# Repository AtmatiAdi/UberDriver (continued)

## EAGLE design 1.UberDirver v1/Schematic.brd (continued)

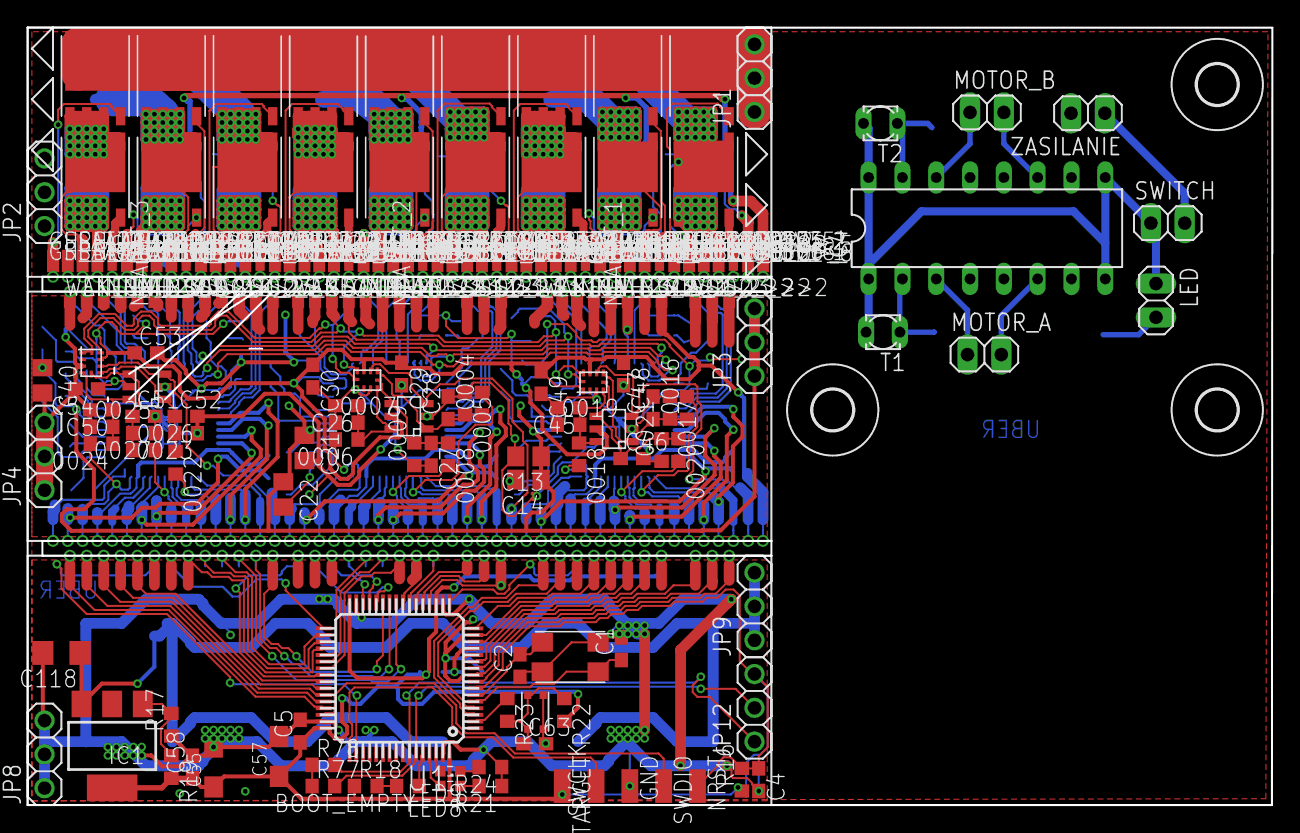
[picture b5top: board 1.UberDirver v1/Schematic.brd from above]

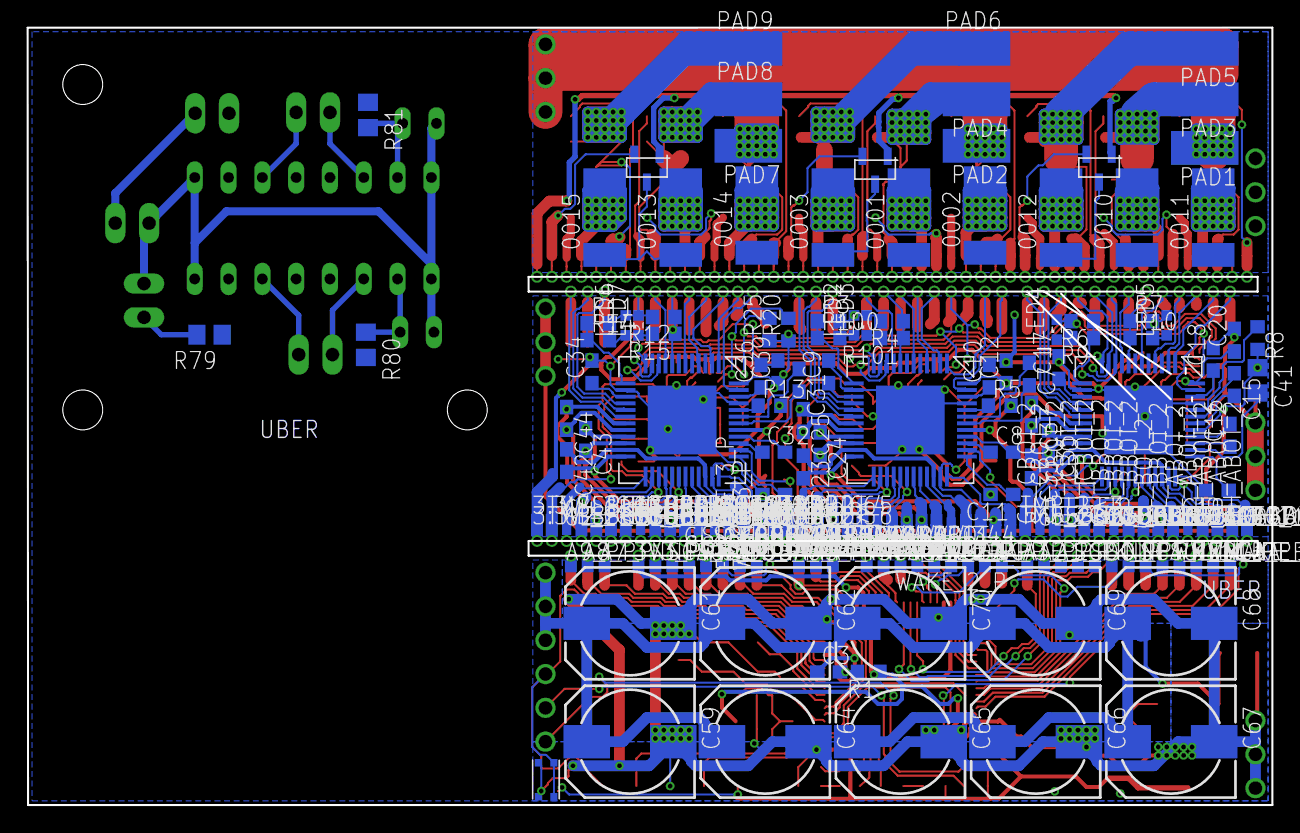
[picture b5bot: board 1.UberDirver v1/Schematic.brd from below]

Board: 2 copper layers, 93.5 x 58.4 mm, 470 parts (225 on the bottom side), 234 nets.

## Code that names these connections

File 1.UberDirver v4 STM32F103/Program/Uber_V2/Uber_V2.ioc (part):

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Mcu.Name=STM32F103T(8-B)Ux
Mcu.Package=VFQFPN36
Mcu.UserName=STM32F103TBUx
PA0-WKUP.GPIOParameters=GPIO_Label
PA0-WKUP.GPIO_Label=ADC_VA
PA0-WKUP.Signal=ADCx_IN0
PA1.GPIOParameters=GPIO_Label
PA1.GPIO_Label=ADC_VB
PA1.Signal=ADCx_IN1
PA10.GPIOParameters=GPIO_Label
PA10.GPIO_Label=LED
PA10.Signal=GPIO_Output
PA11.Mode=Master
PA11.Signal=CAN_RX
PA12.Mode=Master
PA12.Signal=CAN_TX
PA13.Mode=Serial_Wire
PA13.Signal=SYS_JTMS-SWDIO
PA14.Mode=Serial_Wire
PA14.Signal=SYS_JTCK-SWCLK
PA15.GPIOParameters=GPIO_Label
PA15.GPIO_Label=PWM_AH
PA15.Signal=S_TIM2_CH1_ETR
PA2.GPIOParameters=GPIO_Label
PA2.GPIO_Label=INPUT
PA2.Signal=GPIO_Output
PA3.GPIOParameters=GPIO_Label
PA3.GPIO_Label=ADC_VC
PA3.Signal=ADCx_IN3
PA4.GPIOParameters=GPIO_Label
PA4.GPIO_Label=ADC_VMOT
PA4.Signal=ADCx_IN4
PA5.GPIOParameters=GPIO_Label
PA5.GPIO_Label=SPI_SCK
PA5.Mode=Full_Duplex_Master
PA5.Signal=SPI1_SCK
PA6.GPIOParameters=GPIO_Label
PA6.GPIO_Label=SPI_MISO
PA6.Mode=Full_Duplex_Master
PA6.Signal=SPI1_MISO
PA7.GPIOParameters=GPIO_Label
PA7.GPIO_Label=SPI_MOSI
PA7.Mode=Full_Duplex_Master
PA7.Signal=SPI1_MOSI
PA8.GPIOParameters=GPIO_Label
PA8.GPIO_Label=PWM_CL
PA8.Signal=GPIO_Output
PA9.GPIOParameters=GPIO_Label
PA9.GPIO_Label=PWM_CH
PA9.Signal=S_TIM1_CH2
PB0.GPIOParameters=GPIO_Label
PB0.GPIO_Label=ADC_CA
PB0.Signal=ADCx_IN8
PB1.GPIOParameters=GPIO_Label
PB1.GPIO_Label=ADC_CC
PB1.Signal=ADCx_IN9
PB2.GPIOParameters=GPIO_Label
PB2.GPIO_Label=SPI_CS
PB2.Signal=GPIO_Output
PB3.GPIOParameters=GPIO_Label
PB3.GPIO_Label=PWM_AL
PB3.Signal=GPIO_Output
PB4.GPIOParameters=GPIO_Label
PB4.GPIO_Label=PWM_BH
PB4.Signal=S_TIM3_CH1
PB5.GPIOParameters=GPIO_Label
PB5.GPIO_Label=PWM_BL
PB5.Signal=GPIO_Output
PB6.Mode=Asynchronous
PB6.Signal=USART1_TX
PB7.Mode=Asynchronous
PB7.Signal=USART1_RX
PD0-OSC_IN.GPIOParameters=GPIO_Label
PD0-OSC_IN.GPIO_Label=ENGATE
PD0-OSC_IN.Signal=GPIO_Output
PD1-OSC_OUT.GPIOParameters=GPIO_Label
PD1-OSC_OUT.GPIO_Label=NFAULT
PD1-OSC_OUT.Signal=GPIO_Input
RCC.SYSCLKFreq_VALUE=64000000
RCC.SYSCLKSource=RCC_SYSCLKSOURCE_PLLCLK
board=custom

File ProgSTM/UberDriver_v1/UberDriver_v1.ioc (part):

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Mcu.Name=STM32F103R(8-B)Tx
Mcu.Package=LQFP64
Mcu.UserName=STM32F103RBTx
PA0-WKUP.GPIOParameters=GPIO_Label
PA0-WKUP.GPIO_Label=DVR_3_NFAULT
PA0-WKUP.Signal=GPIO_Input
PA1.GPIOParameters=GPIO_Label
PA1.GPIO_Label=DVR_3_C
PA1.Signal=S_TIM2_CH2
PA10.GPIOParameters=GPIO_Label
PA10.GPIO_Label=DVR_1_A
PA10.Signal=S_TIM1_CH3
PA11.GPIOParameters=GPIO_Label
PA11.GPIO_Label=DVR_1_ENGATE
PA11.Signal=GPIO_Output
PA12.GPIOParameters=GPIO_Label
PA12.GPIO_Label=DVR_1_WAKE
PA12.Signal=GPIO_Output
PA13.Mode=Serial_Wire
PA13.Signal=SYS_JTMS-SWDIO
PA14.Mode=Serial_Wire
PA14.Signal=SYS_JTCK-SWCLK
PA15.GPIOParameters=GPIO_Label
PA15.GPIO_Label=DVR_1_NFAULT
PA15.Signal=GPIO_Input
PA2.GPIOParameters=GPIO_Label
PA2.GPIO_Label=DVR_3_B
PA2.Signal=S_TIM2_CH3
PA3.GPIOParameters=GPIO_Label
PA3.GPIO_Label=DVR_3_A
PA3.Signal=S_TIM2_CH4
PA4.GPIOParameters=GPIO_Label
PA4.GPIO_Label=DRV_2_A3
PA4.Signal=ADCx_IN4
PA5.GPIOParameters=GPIO_Label
PA5.GPIO_Label=DRV_2_A2
PA5.Signal=ADCx_IN5
PA6.GPIOParameters=GPIO_Label
PA6.GPIO_Label=DRV_2_A1
PA6.Signal=ADCx_IN6
PA7.GPIOParameters=GPIO_Label
PA7.GPIO_Label=DVR_2_SPI
PA7.Signal=GPIO_Output
PA8.GPIOParameters=GPIO_Label
PA8.GPIO_Label=DVR_1_C
PA8.Signal=S_TIM1_CH1
PA9.GPIOParameters=GPIO_Label
PA9.GPIO_Label=DVR_1_B
PA9.Signal=S_TIM1_CH2
PB0.GPIOParameters=GPIO_Label
PB0.GPIO_Label=DRV_1_A2
PB0.Signal=ADCx_IN8
PB1.GPIOParameters=GPIO_Label
PB1.GPIO_Label=DRV_1_A3
PB1.Signal=ADCx_IN9
PB10.Mode=I2C
PB10.Signal=I2C2_SCL
PB11.Mode=I2C
PB11.Signal=I2C2_SDA
PB12.GPIOParameters=GPIO_Label
PB12.GPIO_Label=DVR_1_SPI
PB12.Signal=GPIO_Output
PB13.Mode=Full_Duplex_Master
PB13.Signal=SPI2_SCK
PB14.Mode=Full_Duplex_Master
PB14.Signal=SPI2_MISO
PB15.Mode=Full_Duplex_Master
PB15.Signal=SPI2_MOSI
PB2.GPIOParameters=GPIO_Label
PB2.GPIO_Label=DVR_2_ENGATE
PB2.Signal=GPIO_Output
PB6.Mode=I2C
PB6.Signal=I2C1_SCL
PB7.Mode=I2C
PB7.Signal=I2C1_SDA
PB8.GPIOParameters=GPIO_Label
PB8.GPIO_Label=LED_BUILTIN
PB8.Signal=GPIO_Output
PB9.GPIOParameters=GPIO_Label
PB9.GPIO_Label=LED_2
PB9.Signal=GPIO_Output
PC0.GPIOParameters=GPIO_Label
PC0.GPIO_Label=DRV_3_A3
PC0.Signal=ADCx_IN10
PC1.GPIOParameters=GPIO_Label
PC1.GPIO_Label=DRV_3_A2
PC1.Signal=ADCx_IN11
PC10.Mode=Asynchronous
PC10.Signal=USART3_TX
PC11.Mode=Asynchronous
PC11.Signal=USART3_RX
PC13-TAMPER-RTC.GPIOParameters=GPIO_Label
PC13-TAMPER-RTC.GPIO_Label=Button
PC13-TAMPER-RTC.Signal=GPIO_Input
PC14-OSC32_IN.GPIOParameters=GPIO_Label
PC14-OSC32_IN.GPIO_Label=DVR_3_WAKE
PC14-OSC32_IN.Signal=GPIO_Output
PC15-OSC32_OUT.GPIOParameters=GPIO_Label
PC15-OSC32_OUT.GPIO_Label=DVR_3_ENGATE
PC15-OSC32_OUT.Signal=GPIO_Output
PC2.GPIOParameters=GPIO_Label
PC2.GPIO_Label=DRV_3_A3
PC2.Signal=ADCx_IN12
PC3.GPIOParameters=GPIO_Label
PC3.GPIO_Label=DVR_3_SPI
PC3.Signal=GPIO_Output
PC4.GPIOParameters=GPIO_Label
PC4.GPIO_Label=DVR_2_NFAULT
PC4.Signal=GPIO_Input
PC5.GPIOParameters=GPIO_Label
PC5.GPIO_Label=DRV_1_A1
PC5.Signal=ADCx_IN15
PC6.GPIOParameters=GPIO_Label
PC6.GPIO_Label=DVR_2_A
PC6.Signal=S_TIM3_CH1
PC7.GPIOParameters=GPIO_Label
PC7.GPIO_Label=DVR_2_B
PC7.Signal=S_TIM3_CH2
PC8.GPIOParameters=GPIO_Label
PC8.GPIO_Label=DVR_2_C
PC8.Signal=S_TIM3_CH3
PC9.GPIOParameters=GPIO_Label
PC9.GPIO_Label=DVR_2_WAKE
PC9.Signal=GPIO_Output
PD0-OSC_IN.Mode=HSE-External-Oscillator
PD0-OSC_IN.Signal=RCC_OSC_IN
PD1-OSC_OUT.Mode=HSE-External-Oscillator
PD1-OSC_OUT.Signal=RCC_OSC_OUT
RCC.SYSCLKFreq_VALUE=72000000
RCC.SYSCLKSource=RCC_SYSCLKSOURCE_PLLCLK
board=UberDriver_v1

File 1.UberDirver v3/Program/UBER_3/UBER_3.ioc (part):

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Mcu.Name=STM32G473C(B-C-E)Ux
Mcu.Package=UFQFPN48
Mcu.UserName=STM32G473CCUx
PA0.Mode=IN1-Single-Ended
PA0.Signal=ADC2_IN1
PA1.Mode=PGA_Internally_Connected
PA1.Signal=OPAMP1_VINP
PA10.Signal=S_TIM1_CH3
PA13.Mode=Serial_Wire
PA13.Signal=SYS_JTMS-SWDIO
PA14.Mode=Serial_Wire
PA14.Signal=SYS_JTCK-SWCLK
PA15.Signal=S_TIM2_CH1
PA2.Mode=IN3-Single-Ended
PA2.Signal=ADC1_IN3
PA3.Mode=PGA_Internally_Connected
PA3.Signal=OPAMP1_VINM0
PA5.Mode=PGA_Internally_Connected
PA5.Signal=OPAMP2_VINM0
PA6.Mode=IN3-Single-Ended
PA6.Signal=ADC2_IN3
PA7.Mode=Full_Duplex_Master
PA7.Signal=SPI1_MOSI
PA8.Signal=S_TIM1_CH1
PA9.Signal=S_TIM1_CH2
PB0.Mode=PGA_Internally_Connected
PB0.Signal=OPAMP2_VINP
PB1.Mode=PGA Connected
PB1.Signal=OPAMP3_VOUT
PB10.Signal=S_TIM2_CH3
PB11.Signal=S_TIM2_CH4
PB12.Mode=IN11-Single-Ended
PB12.Signal=ADC1_IN11
PB13.Mode=PGA Connected
PB13.Signal=OPAMP3_VINP
PB14.Mode=PWM Generation2 CH2 CH2N
PB14.Signal=TIM1_CH2N
PB15.Mode=PWM Generation3 CH3 CH3N
PB15.Signal=TIM1_CH3N
PB2.Mode=PGA Connected
PB2.Signal=OPAMP3_VINM0
PB3.Mode=Full_Duplex_Master
PB3.Signal=SPI1_SCK
PB4.Mode=Full_Duplex_Master
PB4.Signal=SPI1_MISO
PB5.Mode=PWM Generation3 CH3 CH3N
PB5.Signal=TIM8_CH3N
PB6.Mode=Asynchronous
PB6.Signal=USART1_TX
PB7.Mode=Asynchronous
PB7.Signal=USART1_RX
PB8-BOOT0.Signal=S_TIM8_CH2
PB9.Signal=S_TIM8_CH3
PC10.Mode=PWM Generation1 CH1 CH1N
PC10.Signal=TIM8_CH1N
PC11.Mode=PWM Generation2 CH2 CH2N
PC11.Signal=TIM8_CH2N
PC13.Mode=PWM Generation1 CH1 CH1N
PC13.Signal=TIM1_CH1N
PC14-OSC32_IN.GPIOParameters=GPIO_Label
PC14-OSC32_IN.GPIO_Label=ENGATE_1
PC14-OSC32_IN.Signal=GPIO_Output
PC15-OSC32_OUT.GPIOParameters=GPIO_Label
PC15-OSC32_OUT.GPIO_Label=ENGATE_2
PC15-OSC32_OUT.Signal=GPIO_Output
PC4.Mode=IN5-Single-Ended
PC4.Signal=ADC2_IN5
PC6.Signal=S_TIM8_CH1
PF0-OSC_IN.Mode=IN10-Single-Ended
PF0-OSC_IN.Signal=ADC1_IN10
PF1-OSC_OUT.GPIOParameters=GPIO_Label
PF1-OSC_OUT.GPIO_Label=NFAULT_1
PF1-OSC_OUT.Signal=GPIO_Input
PG10-NRST.GPIOParameters=GPIO_Label
PG10-NRST.GPIO_Label=NFAULT_2
PG10-NRST.Signal=GPIO_Input
RCC.HSE_VALUE=8000000
RCC.SYSCLKFreq_VALUE=16000000
board=custom

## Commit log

2020-05-14 Wprowadzono projekt
2020-07-09 Wersja 3
2020-10-13 aktualizacja
2020-11-15 Current is stm32f103 V3
2021-01-28 Inzynier zrobiony
    dodano wersje 3
2021-02-05 Kolejne kolejności
2021-02-05 Clear and clean
2021-02-13 progress
2022-02-27 refresh repo and separate control from main.c
2022-03-01 application and control class
2022-03-03 adc and open loop control fix
    ADC_WRONG_RADINGS - changed voltage divider from 100k/10k to 10k/1k and 15pf cap added. BEMF_OPEN_LOOP_NOT_WORKING - function DElay_Tick was not declared in control.h, fucking strange
2022-03-03 now open loop control is fixed
    in previous commit this declaration was commeneted for tests :p
2022-03-08 zmienne opoznienie, skan danych, zalazek obserwera
2022-03-10 ADC sequence synchronisation
2022-03-13 BEMF and HALL observers !!!
2022-03-13 hall and bemf observers fixes
2022-03-13 preparation for sinusoiidal control
2022-03-20 svm modulation
2022-03-20 svm and tfm, 6 var and 5 traces debugging
2022-03-21 multi traces debugging fix
2022-03-22 LEGENDARY WORKING CODE BY MAGIC REASONS. LEGENDARY KURWA
2022-03-22 WORKS EVEN BETTER CAYSE of observer and comutator synchro
2022-03-24 hall observer improvements
2022-03-24 adc read 32b fix
2022-03-24 BEMF observer performance improvemnts
    max rpm around 27kRPM
2022-03-25 pwm controll implemented
2022-03-25 Instant spin, but simple version and problems can occur
2022-03-28 cleaning application
2022-03-28 alfa beta xdeee
2022-03-31 Oscilograms added
2022-04-11 sim for presentation
2022-04-12 clearings
2022-04-12 working hall v3
2022-04-12 adc multi modes preparation
2022-04-13 preparations to BEMF observer
2022-04-14 BEMF WORKING !!!
2022-04-17 preparation to optimize bemf observer
2022-04-29 spi bugs added :p
2022-04-30 Fast hall observer added
2022-04-30 all algorithms are optimised, bemf startup problems
2022-04-30 additional small improvemts on bemf observer
2022-05-20 some filtration, bemf start seq, diode caonduction nivelation in meas
2022-05-20 preparations to hall + svm
2022-05-21 more svm resolutions
2022-05-23 simulations improvements
2022-05-25 Some svm improvemts
2022-05-25 Ardu for test
2022-05-26 simulation fixes
2022-05-27 svm not soo hot as before
2022-05-30 ardu
2022-06-04 NOT_TESTED some cleaning in code
2022-06-12 sim adjustments
2022-06-24 summary figures
2022-06-24 new summary figure
2022-07-01 meas
2022-07-01 preparations to motor positioning
2023-02-28 cmake added
2023-02-28 Suppress linker warning
